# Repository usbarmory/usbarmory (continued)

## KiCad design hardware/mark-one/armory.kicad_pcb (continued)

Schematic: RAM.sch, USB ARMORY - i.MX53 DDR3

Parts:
C89, C90, C91, C93, C94, C96, C97, C98, C100, C101, C102, C104: 0.1uF; SM0201; Mfg PN C0603X5R0J104K030BC
C95, C99, C103: 0.01uF; SM0201; Mfg PN C0603X7R1A103K030BA
C105, C106: 10uF; SM0603; Mfg PN C1608X5R1A106K080AC
P3: TST; TP
R15, R24: 470; SM0201; Mfg PN CRCW0201470RFNED
R27, R29: 240; SM0201; Mfg PN CRCW0201240RFNED
R30: 100; SM0603; Mfg PN CRCW0603100RFKEA
U2: MX53
U4: MT41K256M16HA; micron-96-fbga-ha; Mfg PN MT41K256M16HA-107

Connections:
/RAM/DDR_VREF: C89.1, C90.2, C91.1, C93.1, P3.1, R15.1, R24.2, U2.L17 (DDR_VREF), U4.H1 (VREFDQ), U4.M8 (VREFCA)
/RAM/DDR_ZQ: R29.2, U4.L8 (ZQ)
/RAM/DRAM_A0: U2.M19 (DRAM_A0), U4.N3 (A0)
/RAM/DRAM_A1: U2.L21 (DRAM_A1), U4.P7 (A1)
/RAM/DRAM_A2: U2.M20 (DRAM_A2), U4.P3 (A2)
/RAM/DRAM_A3: U2.N20 (DRAM_A3), U4.N2 (A3)
/RAM/DRAM_A4: U2.K20 (DRAM_A4), U4.P8 (A4)
/RAM/DRAM_A5: U2.N21 (DRAM_A5), U4.P2 (A5)
/RAM/DRAM_A6: U2.M22 (DRAM_A6), U4.R8 (A6)
/RAM/DRAM_A7: U2.N22 (DRAM_A7), U4.R2 (A7)
/RAM/DRAM_A8: U2.N23 (DRAM_A8), U4.T8 (A8)
/RAM/DRAM_A9: U2.M21 (DRAM_A9), U4.R3 (A9)
/RAM/DRAM_A10: U2.K19 (DRAM_A10), U4.L7 (A10/AP)
/RAM/DRAM_A11: U2.L22 (DRAM_A11), U4.R7 (A11)
/RAM/DRAM_A12: U2.L20 (DRAM_A12), U4.N7 (A12/~BC)
/RAM/DRAM_A13: U2.L23 (DRAM_A13), U4.T3 (A13)
/RAM/DRAM_A14: U2.N18 (DRAM_A14), U4.T7 (A14)
/RAM/DRAM_CALIBRATION: R27.2, U2.M23 (DRAM_CALIBRATION)
/RAM/DRAM_CAS: U2.L18 (DRAM_CAS), U4.K3 (~CAS)
/RAM/DRAM_CS0: U2.K18 (DRAM_CS0), U4.L2 (~CS)
/RAM/DRAM_D0: U2.H20 (DRAM_D0), U4.E3 (DQ0)
/RAM/DRAM_D1: U2.G21 (DRAM_D1), U4.F7 (DQ1)
/RAM/DRAM_D2: U2.J21 (DRAM_D2), U4.F2 (DQ2)
/RAM/DRAM_D3: U2.G20 (DRAM_D3), U4.F8 (DQ3)
/RAM/DRAM_D4: U2.J23 (DRAM_D4), U4.H3 (DQ4)
/RAM/DRAM_D5: U2.G23 (DRAM_D5), U4.H8 (DQ5)
/RAM/DRAM_D6: U2.J22 (DRAM_D6), U4.G2 (DQ6)
/RAM/DRAM_D7: U2.G22 (DRAM_D7), U4.H7 (DQ7)
/RAM/DRAM_D8: U2.E21 (DRAM_D8), U4.D7 (DQ8)
/RAM/DRAM_D9: U2.D21 (DRAM_D9), U4.C3 (DQ9)
/RAM/DRAM_D10: U2.E22 (DRAM_D10), U4.C8 (DQ10)
/RAM/DRAM_D11: U2.D20 (DRAM_D11), U4.C2 (DQ11)
/RAM/DRAM_D12: U2.E23 (DRAM_D12), U4.A7 (DQ12)
/RAM/DRAM_D13: U2.C23 (DRAM_D13), U4.A2 (DQ13)
/RAM/DRAM_D14: U2.F23 (DRAM_D14), U4.B8 (DQ14)
/RAM/DRAM_D15: U2.C22 (DRAM_D15), U4.A3 (DQ15)
/RAM/DRAM_DQM0: U2.H21 (DRAM_DQM0), U4.E7 (LDM)
/RAM/DRAM_DQM1: U2.E20 (DRAM_DQM1), U4.D3 (UDM)
/RAM/DRAM_RAS: U2.J19 (DRAM_RAS), U4.J3 (~RAS)
/RAM/DRAM_RESET: U2.P18 (DRAM_RESET), U4.T2 (~RESET)
/RAM/DRAM_SDBA0: U2.R19 (DRAM_SDBA0), U4.M2 (BA0)
/RAM/DRAM_SDBA1: U2.P20 (DRAM_SDBA1), U4.N8 (BA1)
/RAM/DRAM_SDBA2: U2.N19 (DRAM_SDBA2), U4.M3 (BA2)
/RAM/DRAM_SDCKE0: U2.H19 (DRAM_SDCKE0), U4.K9 (CKE)
/RAM/DRAM_SDCLK_0: R30.1, U2.K23 (DRAM_SDCLK_0), U4.J7 (CK)
/RAM/DRAM_SDCLK_0_B: R30.2, U2.K22 (~DRAM_SDCLK_0_B), U4.K7 (~CK)
/RAM/DRAM_SDODT0: U2.J18 (DRAM_SDODT0), U4.K1 (ODT)
/RAM/DRAM_SDQS0: U2.H23 (DRAM_SDQS0), U4.F3 (LDQS)
/RAM/DRAM_SDQS0_B: U2.H22 (~DRAM_SDQS0_B), U4.G3 (~LDQS)
/RAM/DRAM_SDQS1: U2.D23 (DRAM_SDQS1), U4.C7 (UDQS)
/RAM/DRAM_SDQS1_B: U2.D22 (~DRAM_SDQS1_B), U4.B7 (~UDQS)
/RAM/DRAM_WE: U2.L19 (DRAM_SDWE), U4.L3 (~WE)
GND: C89.2, C91.2, C93.2, C94.2, C95.2, C96.2, C97.2, C98.2, C99.2, C100.2, C101.2, C102.2, C103.2, C104.2, C105.2, C106.2, R24.1, R27.1, R29.1, U4.A9 (VSS1), U4.B1 (VSSQ1), U4.B3 (VSS2), U4.B9 (VSSQ2), U4.D1 (VSSQ3), U4.D8 (VSSQ4), U4.E1 (VSS3), U4.E2 (VSSQ5), U4.E8 (VSSQ6), U4.F9 (VSSQ7), U4.G1 (VSSQ8), U4.G8 (VSS4), U4.G9 (VSSQ9), U4.J2 (VSS5), U4.J8 (VSS6), U4.M9 (VSS8), U4.P1 (VSS9), U4.P9 (VSS10), U4.T1 (VSS11), U4.T9 (VSS12); also elsewhere on the board
PMIC_DDR_1V5: C90.1, C94.1, C95.1, C96.1, C97.1, C98.1, C99.1, C100.1, C101.1, C102.1, C103.1, C104.1, C105.1, C106.1, R15.2, U4.A1 (VDDQ1), U4.A8 (VDDQ2), U4.B2 (VDD1), U4.C1 (VDDQ3), U4.C9 (VDDQ4), U4.D2 (VDDQ5), U4.D9 (VDD2), U4.E9 (VDDQ6), U4.F1 (VDDQ7), U4.G7 (VDD3), U4.H2 (VDDQ8), U4.H9 (VDDQ9), U4.K2 (VDD4), U4.K8 (VDD5), U4.N1 (VDD6), U4.N9 (VDD7), U4.R1 (VDD8), U4.R9 (VDD9); also elsewhere on the board

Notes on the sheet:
Place near the VDD balls.
Place near the VDDQ balls.

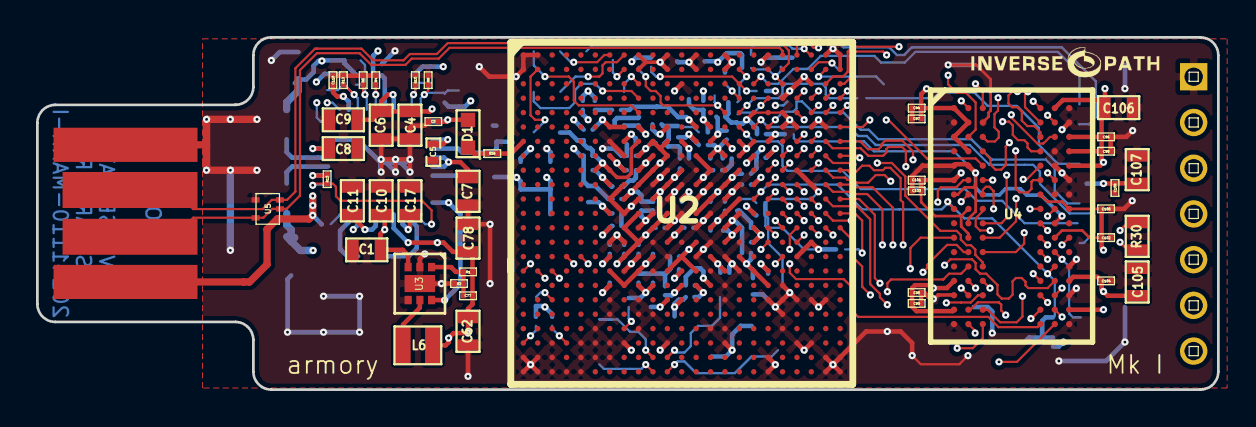
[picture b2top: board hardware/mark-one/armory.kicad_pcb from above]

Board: 8 copper layers, 65.6 x 19.6 mm, 186 parts (0 on the bottom side), 126 nets.

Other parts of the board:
Ref**: Val**; LOGO_SMALL

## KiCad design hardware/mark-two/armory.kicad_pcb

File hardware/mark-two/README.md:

Introduction
============

The USB armory is an open source hardware design, implementing a flash drive
sized computer.

This repository is aimed towards developers, if you wish to purchase a USB
armory board please see the [ordering information](https://github.com/usbarmory/usbarmory/wiki/Ordering-information).

Authors
=======

Andrea Barisani  
andrea@inversepath.com  

Andrej Rosano  
andrej@inversepath.com  

Daniele Bianco  
daniele@inversepath.com  

Documentation
=============

The main documentation can be found on the
[project wiki](https://github.com/usbarmory/usbarmory/wiki).

Revision information
====================

This directory contains the hardware design for the USB armory Mk II rev. γ.

Current schematics and layout files have been designed in KiCad 5.1.10.

PCB Information
===============

6 layers, 0.8mm thickness  
Outer layers 0.5 oz base copper foil  
Inner layers   1 oz base copper foil  
width (X) 65.6 mm, height (Y) 19.5 mm  
Electroless Nickel Immersion Gold (ENIG) surface finish  
Black resist, white component legend

Layers
------

Order and type of copper layers:  
  TOP:         signal, front components  
  SIGNAL 1:    signal  
  GND POWER 1: ground and power plane  
  GND POWER 2: ground and power plane  
  SIGNAL 2:    signal  
  BOTTOM:      signal, back components  

| Layer | Description               |  Thickness (in um)  |
|:-----:|---------------------------|:-------------------:|
|       | LPI mask                  |   15                |
|       | ENIG plating              |   18                |
|   1   | copper                    |   30                |
|       | prepreg, 2 x PP 106       |  121                |
|   2   | copper                    |   17                |
|       | core, FR4 17/17           |  125                |
|   3   | copper                    |   17                |
|       | prepreg, 2 x PP 106       |  116                |
|   4   | copper                    |   17                |
|       | core, FR4 17/17           |  125                |
|   5   | copper                    |   17                |
|       | prepreg, 2 x PP 106       |  121                |
|   6   | copper                    |   30                |
|       | ENIG plating              |   18                |
|       | LPI mask                  |   15                |

Material: Isola PCL370-HR
Total thickness: 0.8 mm

DRC information
---------------

Minimum track width:            0.100 mm  
Minimum via diameter:           0.406 mm  
Outer layer track width:        0.100 mm  
Outer layer isolation distance: 0.100 mm  
Outer layer annular ring:       0.075 mm  
Inner layer track width:        0.100 mm  
Inner layer isolation distance: 0.100 mm  
Inner layer annular ring:       0.075 mm  
Smallest final hole (plated):   0.150 mm

Regulatory compliance & handling
================================

The USB armory board is an open system design, which does not include a
shielded enclosure. This may cause interference to other electrical or
electronic devices in close proximity. In a domestic environment, this product
may cause radio interference in which case the user may be required to take
adequate measures. In addition, this board should not be used near any medical
equipment or RF devices.

The board is sensitive to Electrostatic discharge (ESD). Hold the board only by
its edges. After removing the board from its box, place it on a grounded,
static-free surface.

The board can become hot, like any fan-less design, during continuous high CPU
loads, mind its temperature while handling it.

* [Compliance information](https://github.com/usbarmory/usbarmory/wiki/Compliance-information)

License
=======

USB armory | https://github.com/usbarmory/usbarmory  
Copyright (c) The USB armory authors

This source describes Open Hardware and is licensed under the CERN-OHL-S v2.

You may redistribute and modify this source and make products using it under
the terms of the CERN-OHL-S v2 (https://ohwr.org/cern_ohl_s_v2.txt).

This source is distributed WITHOUT ANY EXPRESS OR IMPLIED WARRANTY, INCLUDING
OF MERCHANTABILITY, SATISFACTORY QUALITY AND FITNESS FOR A PARTICULAR PURPOSE.
Please see the CERN-OHL-S v2 for applicable conditions.

As per CERN-OHL-S v2 section 4, should You produce hardware based on this
source, You must where practicable maintain the Source Location visible on the
external case of the USB armory or other products you make using this source.

The following exceptions apply:

- `../lib.snapeda`: all files in this directory are imported or modified
  from SnapEDA symbols and footprints, therefore the license at
  https://www.snapeda.com/about/FAQ/#license applies.

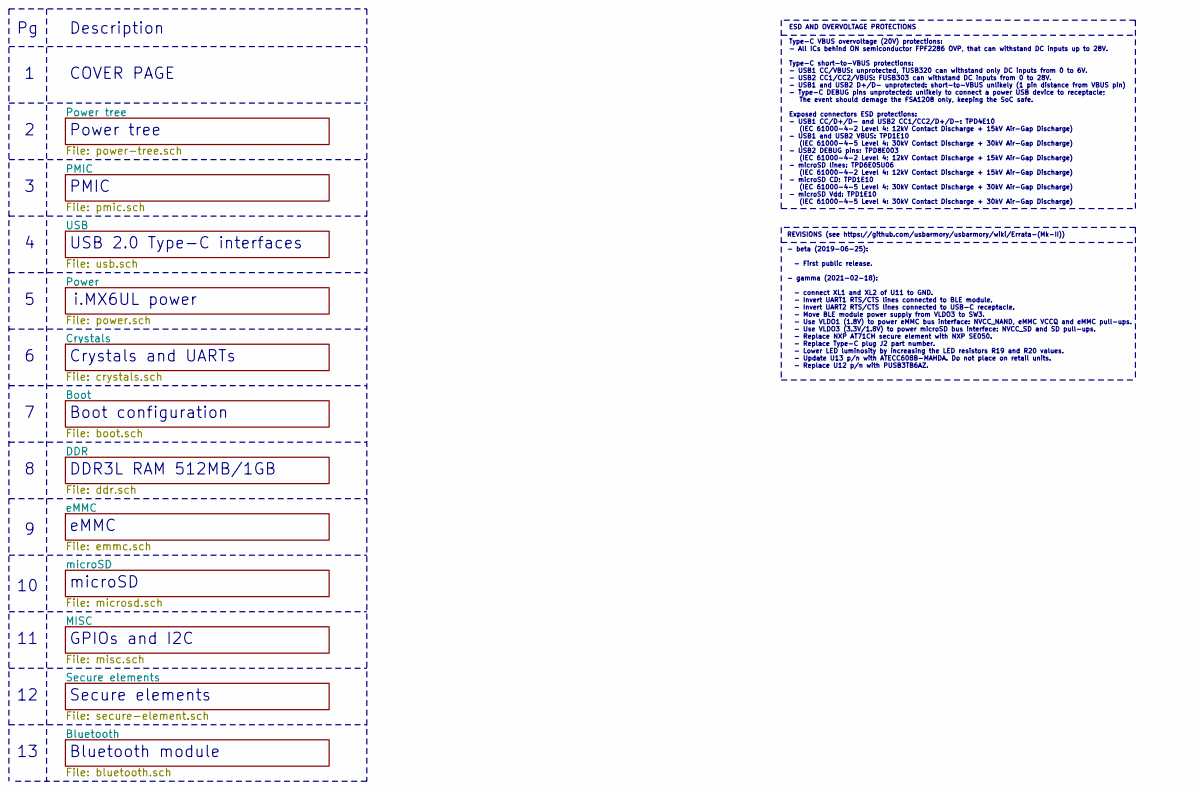
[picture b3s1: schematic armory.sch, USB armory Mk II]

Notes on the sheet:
microSD
DDR3L RAM 512MB/1GB
eMMC
Secure elements
Bluetooth module
Boot configuration
GPIOs and I2C
i.MX6UL power
USB 2.0 Type-C interfaces
Crystals and UARTs
ESD AND OVERVOLTAGE PROTECTIONS Type-C VBUS overvoltage (20V) protections: - All ICs behind ON semiconductor FPF2286 OVP, that can withstand DC inputs up to 28V. Type-C short-to-VBUS protections: - USB1 CC/VBUS: unprotected, TUSB320 can withstand only DC inputs from 0 to 6V. - USB2 CC1/CC2/VBUS: FU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
PMIC
Description
Power tree
COVER PAGE
REVISIONS (see https://github.com/usbarmory/usbarmory/wiki/Errata-(Mk-II)) - beta (2019-06-25): - First public release. - gamma (2021-02-18): - connect XL1 and XL2 of U11 to GND. - Invert UART1 RTS/CTS lines connected to BLE module. - Invert UART2 RTS/CTS lines connected to USB-C receptacle. - Move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

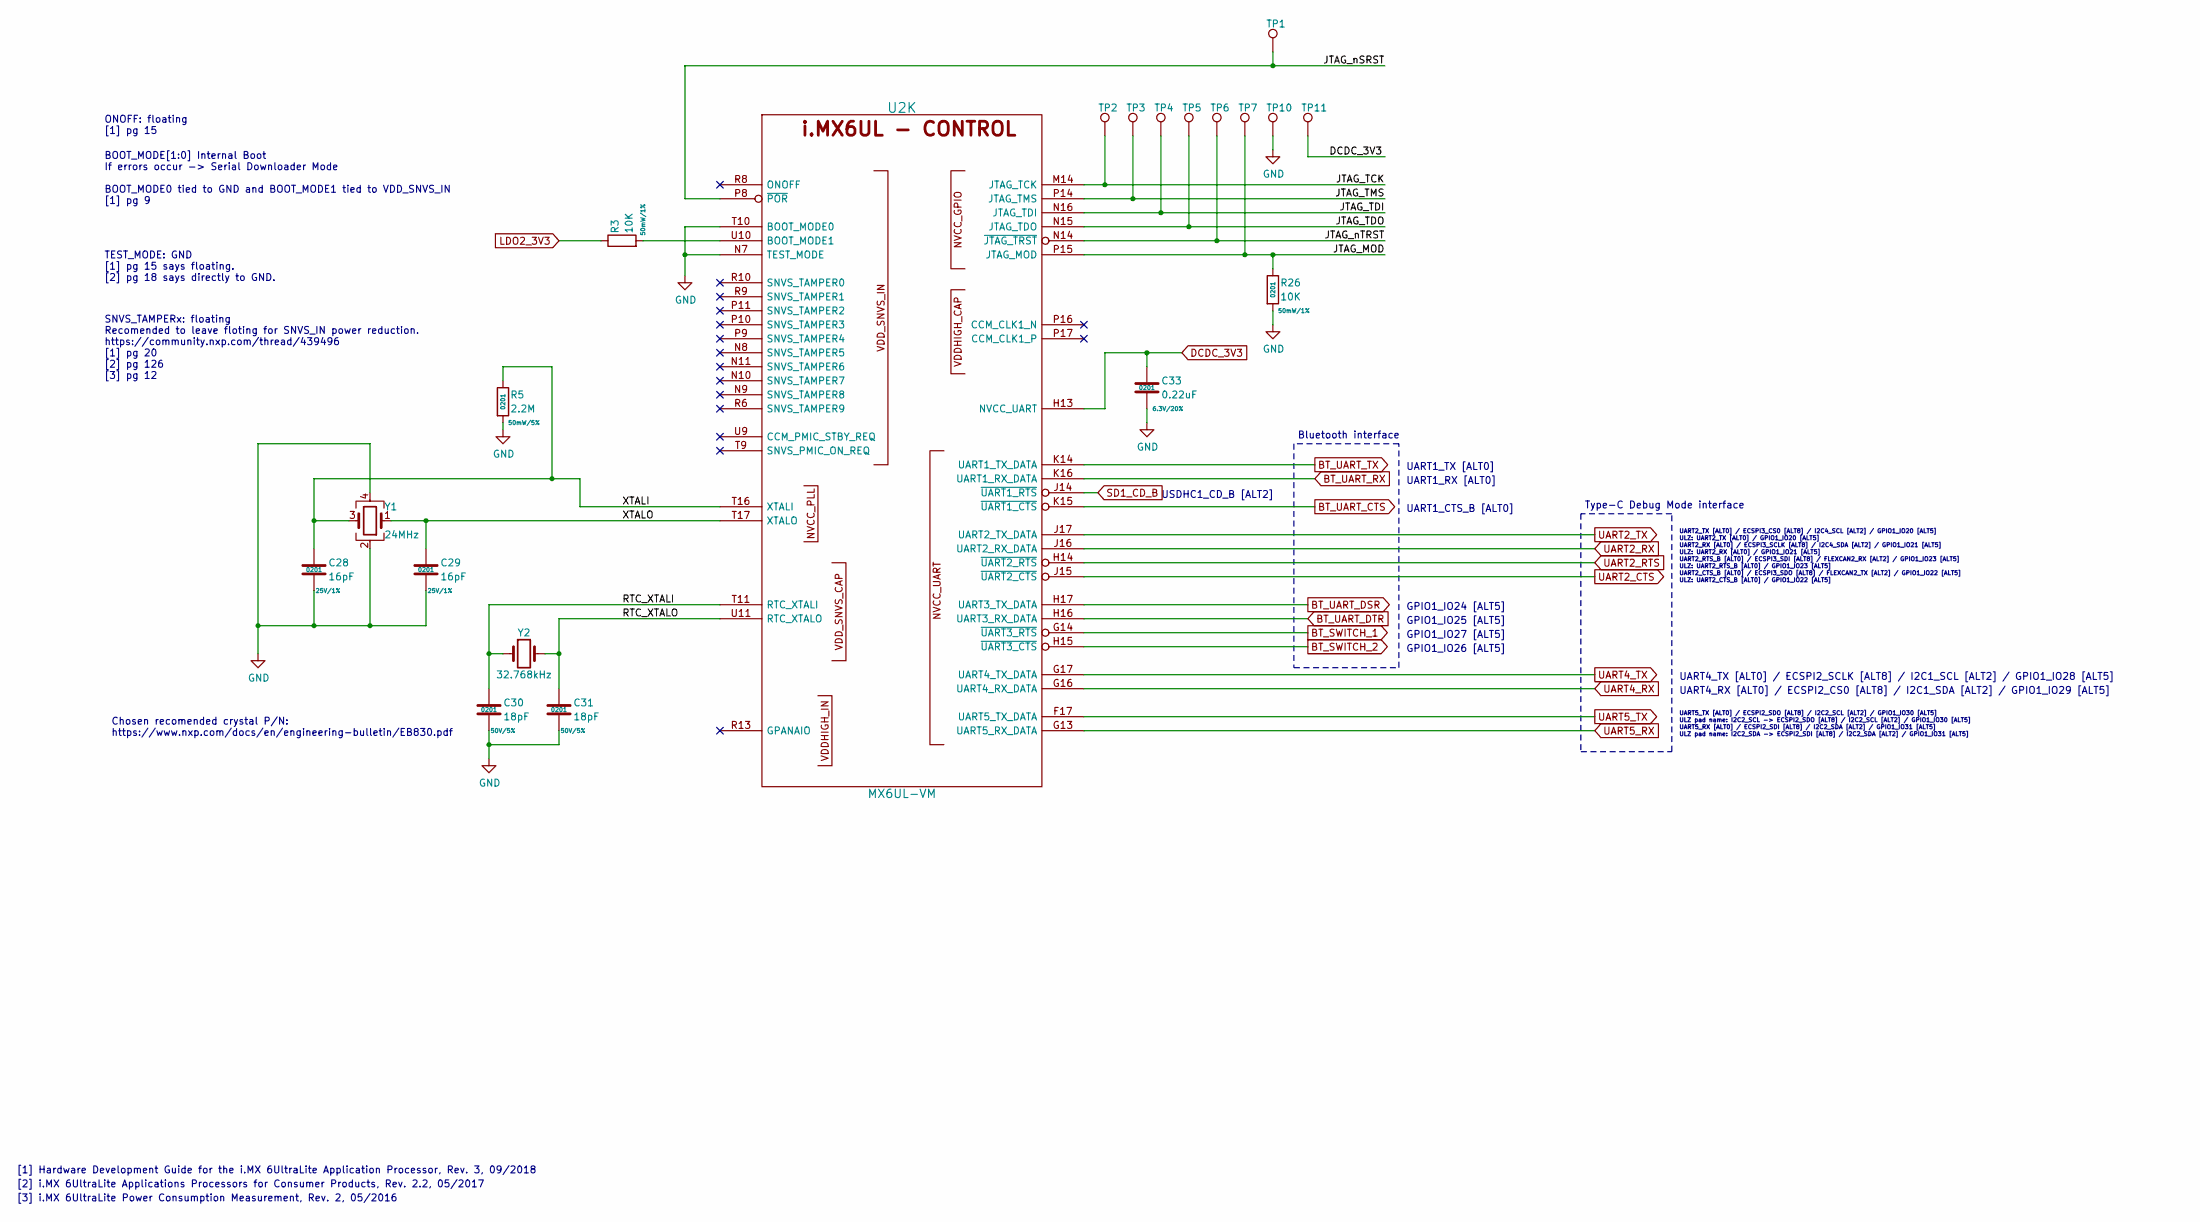
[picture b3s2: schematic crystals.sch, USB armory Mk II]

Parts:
C28, C29: 16pF; SM0201; Rating 25V/1%; Mfg PN CBR02C160F3GAC
C30, C31: 18pF; SM0201; Rating 50V/5%; Mfg PN GRM0335C1H180JA01D
C33: 0.22uF; SM0201; Rating 6.3V/20%; Mfg PN GRM033R60J224ME15D
R3, R26: 10K; SM0201; Rating 50mW/1%; Mfg PN CRCW020110K0JNED
R5: 2.2M; SM0201; Rating 50mW/5%; Mfg PN RC0201JR-072M2L
TP1, TP2, TP3, TP4, TP5, TP6, TP7, TP10, TP11: TestPoint; TP
U2: MX6UL-VM; SOT1534-2; Mfg PN MCIMX6Z0DVM09AB
Y1: 24MHz; TSX-3225; Mfg PN TSX-3225 24.0000MF15X-AC3
Y2: 32.768kHz; CM7V-T1A; Mfg PN CM7V-T1A-32.768kHz-12.5pF-20PPM-TA-QC

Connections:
/Crystals/JTAG_MOD: R26.1, TP7.1, U2.P15 (JTAG_MOD)
/Crystals/JTAG_TCK: TP2.1, U2.M14 (JTAG_TCK)
/Crystals/JTAG_TDI: TP4.1, U2.N16 (JTAG_TDI)
/Crystals/JTAG_TDO: TP5.1, U2.N15 (JTAG_TDO)
/Crystals/JTAG_TMS: TP3.1, U2.P14 (JTAG_TMS)
/Crystals/JTAG_nSRST: TP1.1, U2.P8 (~POR)
/Crystals/JTAG_nTRST: TP6.1, U2.N14 (~JTAG_TRST)
/Crystals/RTC_XTALI: C30.1, U2.T11 (RTC_XTALI), Y2.1
/Crystals/RTC_XTALO: C31.1, U2.U11 (RTC_XTALO), Y2.2
/Crystals/XTALI: C28.1, R5.1, U2.T16 (XTALI), Y1.3
/Crystals/XTALO: C29.1, U2.T17 (XTALO), Y1.1
BT_SWITCH_1: U2.G14 (~UART3_RTS); also elsewhere on the board
BT_SWITCH_2: U2.H15 (~UART3_CTS); also elsewhere on the board
BT_UART_CTS: U2.K15 (~UART1_CTS); also elsewhere on the board
BT_UART_DSR: U2.H17 (UART3_TX_DATA); also elsewhere on the board
BT_UART_DTR: U2.H16 (UART3_RX_DATA); also elsewhere on the board
BT_UART_RX: U2.K16 (UART1_RX_DATA); also elsewhere on the board
BT_UART_TX: U2.K14 (UART1_TX_DATA); also elsewhere on the board
DCDC_3V3: C33.1, TP11.1, U2.H13 (NVCC_UART); also elsewhere on the board
GND: C28.2, C29.2, C30.2, C31.2, C33.2, R5.2, R26.2, TP10.1, U2.N7 (TEST_MODE), U2.T10 (BOOT_MODE0), Y1.2, Y1.4; also elsewhere on the board
LDO2_3V3: R3.1; also elsewhere on the board
unnamed: R3.2, U2.U10 (BOOT_MODE1)
SD1_CD_B: U2.J14 (~UART1_RTS); also elsewhere on the board
UART2_CTS: U2.J15 (~UART2_CTS); also elsewhere on the board
UART2_RTS: U2.H14 (~UART2_RTS); also elsewhere on the board
UART2_RX: U2.J16 (UART2_RX_DATA); also elsewhere on the board
UART2_TX: U2.J17 (UART2_TX_DATA); also elsewhere on the board
UART4_RX: U2.G16 (UART4_RX_DATA); also elsewhere on the board
UART4_TX: U2.G17 (UART4_TX_DATA); also elsewhere on the board
UART5_RX: U2.G13 (UART5_RX_DATA); also elsewhere on the board
UART5_TX: U2.F17 (UART5_TX_DATA); also elsewhere on the board

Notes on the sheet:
BOOT_MODE[1:0] Internal Boot If errors occur -> Serial Downloader Mode BOOT_MODE0 tied to GND and BOOT_MODE1 tied to VDD_SNVS_IN [1] pg 9
TEST_MODE: GND [1] pg 15 says floating. [2] pg 18 says directly to GND.
[1] Hardware Development Guide for the i.MX 6UltraLite Application Processor, Rev. 3, 09/2018
SNVS_TAMPERx: floating Recomended to leave floting for SNVS_IN power reduction. https://community.nxp.com/thread/439496 [1] pg 20 [2] pg 126 [3] pg 12
[2] i.MX 6UltraLite Applications Processors for Consumer Products, Rev. 2.2, 05/2017
Bluetooth interface
GPIO1_IO24 [ALT5]
GPIO1_IO25 [ALT5]
GPIO1_IO26 [ALT5]
GPIO1_IO27 [ALT5]
UART1_TX [ALT0]
UART1_CTS_B [ALT0]
ONOFF: floating [1] pg 15
[3] i.MX 6UltraLite Power Consumption Measurement, Rev. 2, 05/2016
UART1_RX [ALT0]
USDHC1_CD_B [ALT2]
ULZ pad name: I2C2_SDA -> ECSPI2_SDI [ALT8] / I2C2_SDA [ALT2] / GPIO1_IO31 [ALT5]
ULZ pad name: I2C2_SCL -> ECSPI2_SDO [ALT8] / I2C2_SCL [ALT2] / GPIO1_IO30 [ALT5]
UART4_TX [ALT0] / ECSPI2_SCLK [ALT8] / I2C1_SCL [ALT2] / GPIO1_IO28 [ALT5]
ULZ: UART2_CTS_B [ALT0] / GPIO1_IO22 [ALT5]
ULZ: UART2_RTS_B [ALT0] / GPIO1_IO23 [ALT5]
ULZ: UART2_RX [ALT0] / GPIO1_IO21 [ALT5]
Type-C Debug Mode interface
UART5_RX [ALT0] / ECSPI2_SDI [ALT8] / I2C2_SDA [ALT2] / GPIO1_IO31 [ALT5]
UART5_TX [ALT0] / ECSPI2_SDO [ALT8] / I2C2_SCL [ALT2] / GPIO1_IO30 [ALT5]
UART4_RX [ALT0] / ECSPI2_CS0 [ALT8] / I2C1_SDA [ALT2] / GPIO1_IO29 [ALT5]
UART2_RTS_B [ALT0] / ECSPI3_SDI [ALT8] / FLEXCAN2_RX [ALT2] / GPIO1_IO23 [ALT5]
UART2_CTS_B [ALT0] / ECSPI3_SDO [ALT8] / FLEXCAN2_TX [ALT2] / GPIO1_IO22 [ALT5]
UART2_RX [ALT0] / ECSPI3_SCLK [ALT8] / I2C4_SDA [ALT2] / GPIO1_IO21 [ALT5]
UART2_TX [ALT0] / ECSPI3_CS0 [ALT8] / I2C4_SCL [ALT2] / GPIO1_IO20 [ALT5]
ULZ: UART2_TX [ALT0] / GPIO1_IO20 [ALT5]
Chosen recomended crystal P/N: https://www.nxp.com/docs/en/engineering-bulletin/EB830.pdf

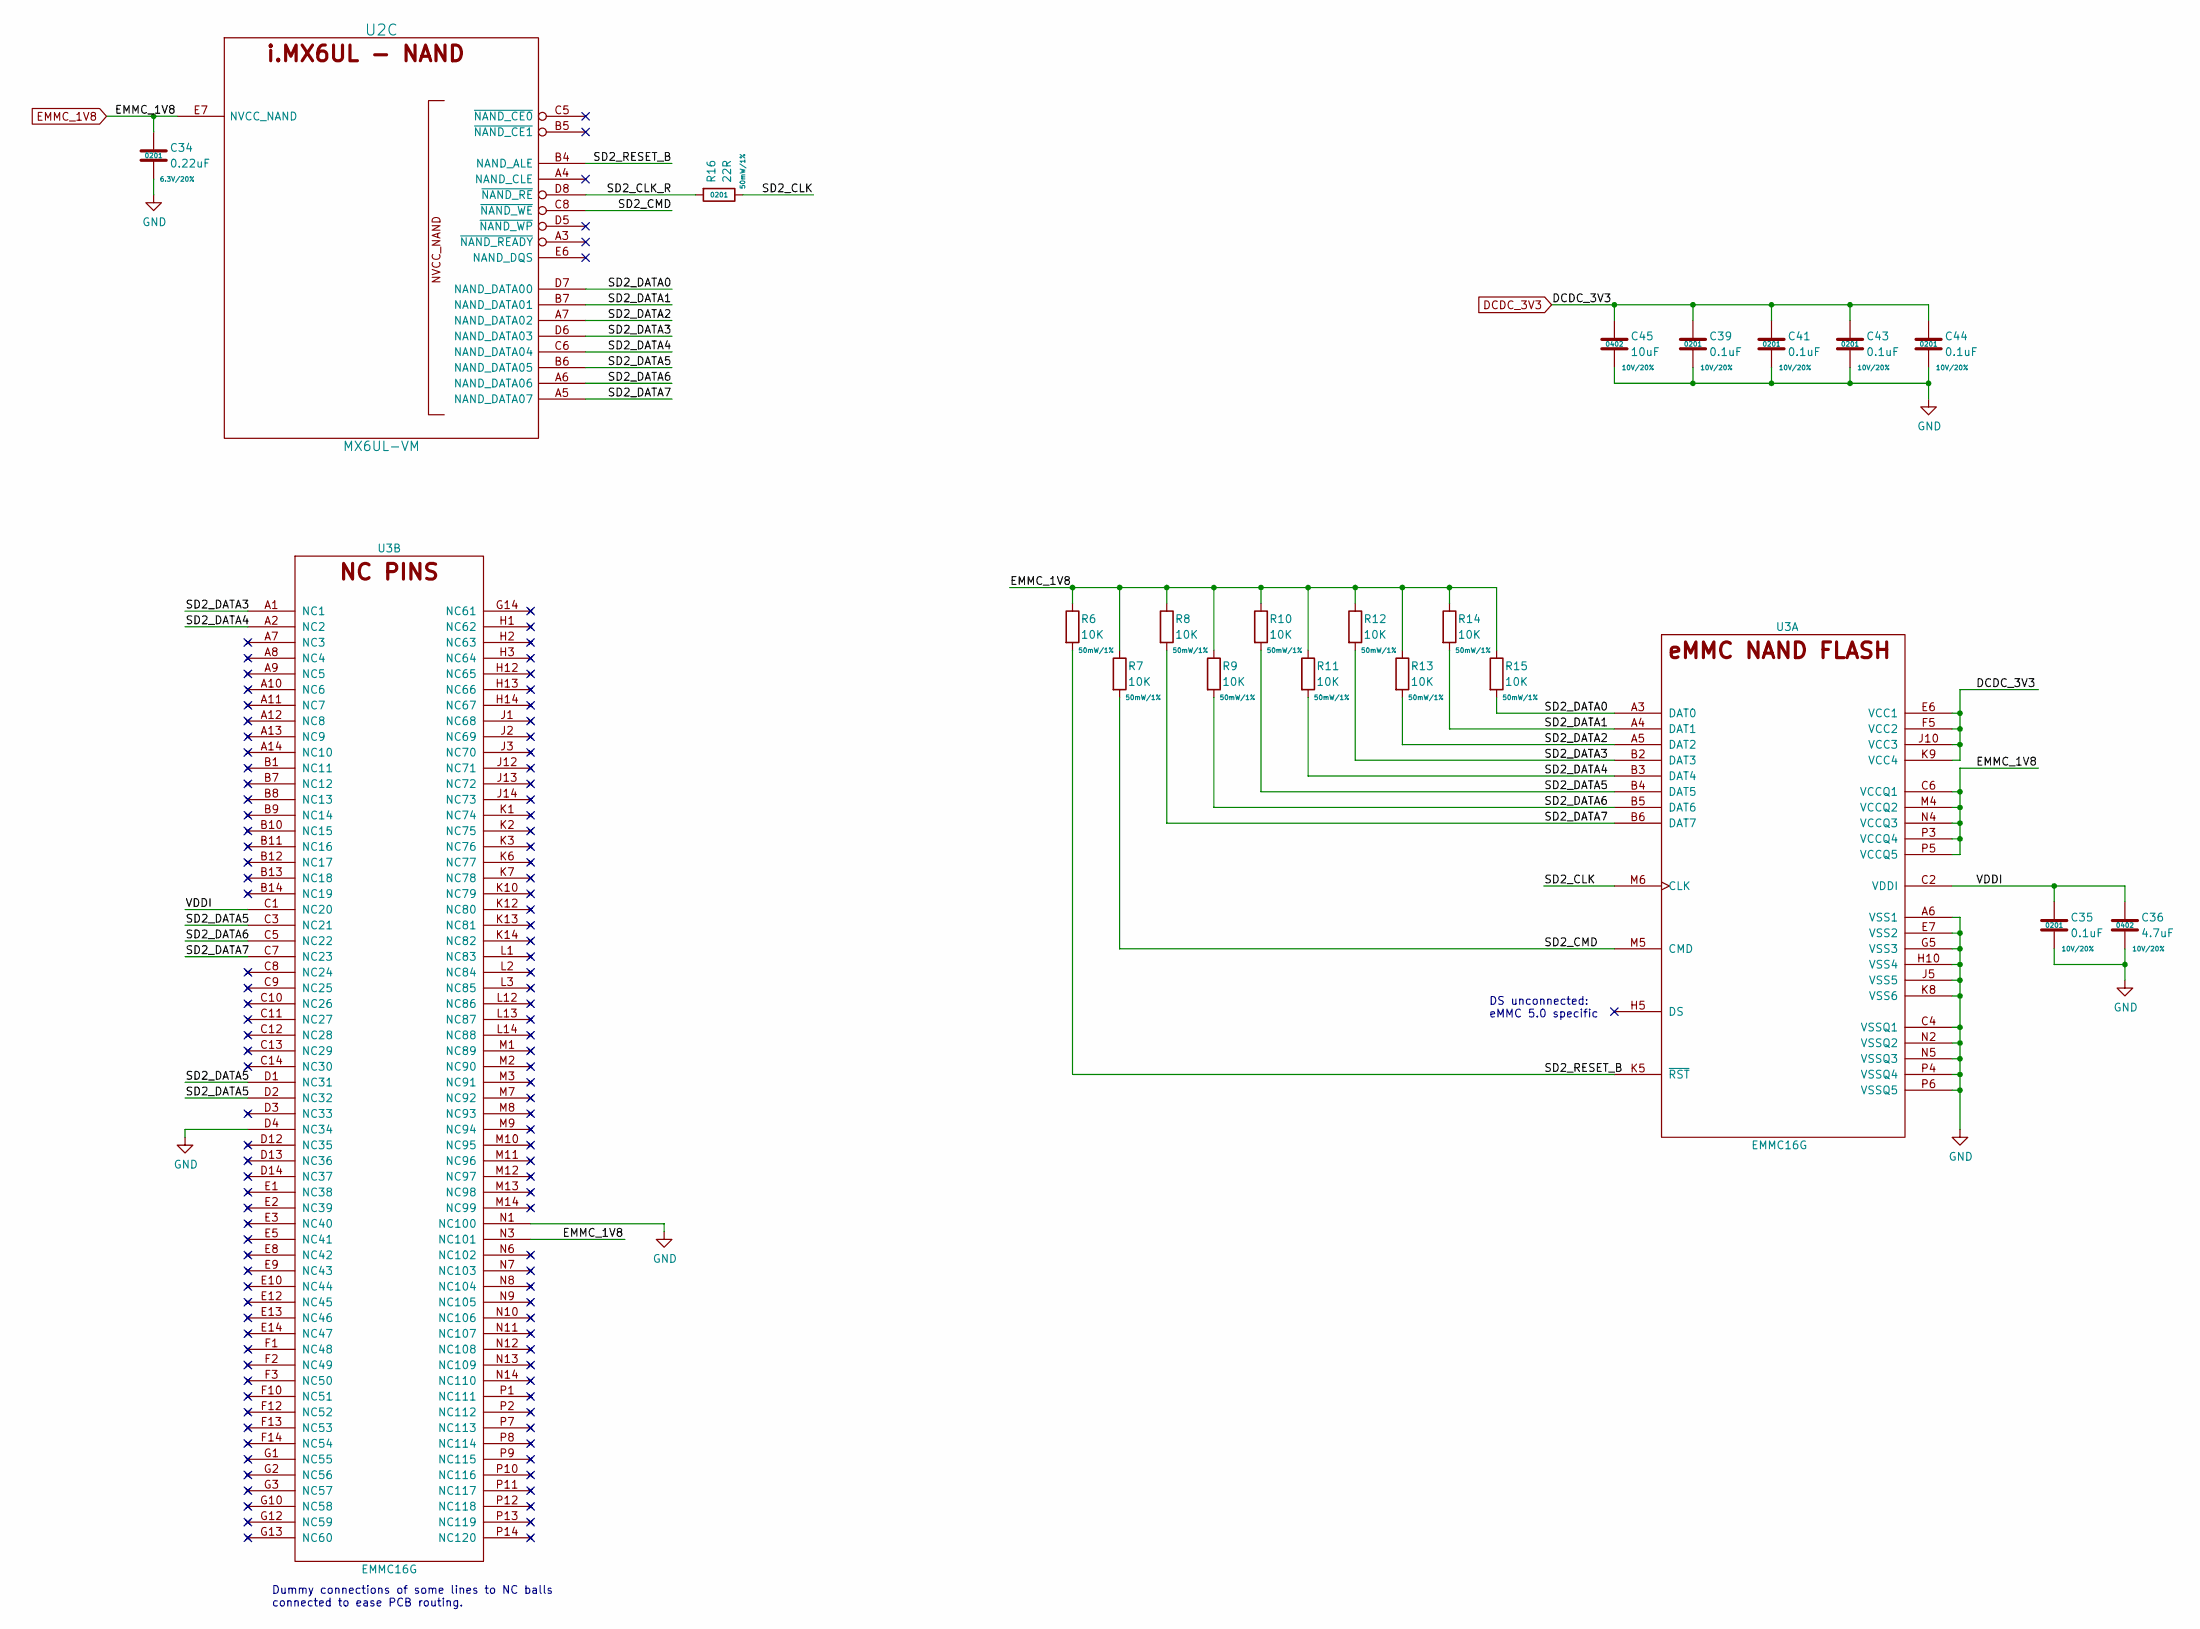
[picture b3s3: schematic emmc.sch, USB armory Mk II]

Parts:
C34: 0.22uF; SM0201; Rating 6.3V/20%; Mfg PN GRM033R60J224ME15D
C35, C39, C41, C43, C44: 0.1uF; SM0201; Rating 10V/20%; Mfg PN GRM033R61A104ME15D
C36: 4.7uF; SM0402; Rating 10V/20%; Mfg PN ZRB15XR61A475ME01D
C45: 10uF; SM0402; Rating 10V/20%; Mfg PN CL05A106MP8NUB8
R6, R7, R8, R9, R10, R11, R12, R13, R14, R15: 10K; SM0201; Rating 50mW/1%; Mfg PN CRCW020110K0JNED
R16: 22R; SM0201; Rating 50mW/1%; Mfg PN CRCW020122R0JNED
U2: MX6UL-VM; SOT1534-2; Mfg PN MCIMX6Z0DVM09AB
U3: EMMC16G; FBGA-153; Mfg PN EMMC16G-TB29-PZ90

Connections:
/eMMC/SD2_CLK: R16.1, U3.M6 (CLK)
/eMMC/SD2_CLK_R: R16.2, U2.D8 (~NAND_RE)
/eMMC/SD2_CMD: R7.2, U2.C8 (~NAND_WE), U3.M5 (CMD)
/eMMC/SD2_DATA0: R15.2, U2.D7 (NAND_DATA00), U3.A3 (DAT0)
/eMMC/SD2_DATA1: R14.2, U2.B7 (NAND_DATA01), U3.A4 (DAT1)
/eMMC/SD2_DATA2: R13.2, U2.A7 (NAND_DATA02), U3.A5 (DAT2)
/eMMC/SD2_DATA3: R12.2, U2.D6 (NAND_DATA03), U3.A1 (NC1), U3.B2 (DAT3)
/eMMC/SD2_DATA4: R11.2, U2.C6 (NAND_DATA04), U3.A2 (NC2), U3.B3 (DAT4)
/eMMC/SD2_DATA5: R10.2, U2.B6 (NAND_DATA05), U3.B4 (DAT5), U3.C3 (NC21), U3.D1 (NC31), U3.D2 (NC32)
/eMMC/SD2_DATA6: R9.2, U2.A6 (NAND_DATA06), U3.B5 (DAT6), U3.C5 (NC22)
/eMMC/SD2_DATA7: R8.2, U2.A5 (NAND_DATA07), U3.B6 (DAT7), U3.C7 (NC23)
/eMMC/SD2_RESET_B: R6.2, U2.B4 (NAND_ALE), U3.K5 (~RST)
/eMMC/VDDI: C35.1, C36.1, U3.C1 (NC20), U3.C2 (VDDI)
DCDC_3V3: C39.1, C41.1, C43.1, C44.1, C45.1, U3.E6 (VCC1), U3.F5 (VCC2), U3.J10 (VCC3), U3.K9 (VCC4); also elsewhere on the board
EMMC_1V8: C34.1, R6.1, R7.1, R8.1, R9.1, R10.1, R11.1, R12.1, R13.1, R14.1, R15.1, U2.E7 (NVCC_NAND), U3.C6 (VCCQ1), U3.M4 (VCCQ2), U3.N3 (NC101), U3.N4 (VCCQ3), U3.P3 (VCCQ4), U3.P5 (VCCQ5); also elsewhere on the board
GND: C34.2, C35.2, C36.2, C39.2, C41.2, C43.2, C44.2, C45.2, U3.A6 (VSS1), U3.C4 (VSSQ1), U3.D4 (NC34), U3.E7 (VSS2), U3.G5 (VSS3), U3.H10 (VSS4), U3.J5 (VSS5), U3.K8 (VSS6), U3.N1 (NC100), U3.N2 (VSSQ2), U3.N5 (VSSQ3), U3.P4 (VSSQ4), U3.P6 (VSSQ5); also elsewhere on the board

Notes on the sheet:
Dummy connections of some lines to NC balls connected to ease PCB routing.
DS unconnected: eMMC 5.0 specific

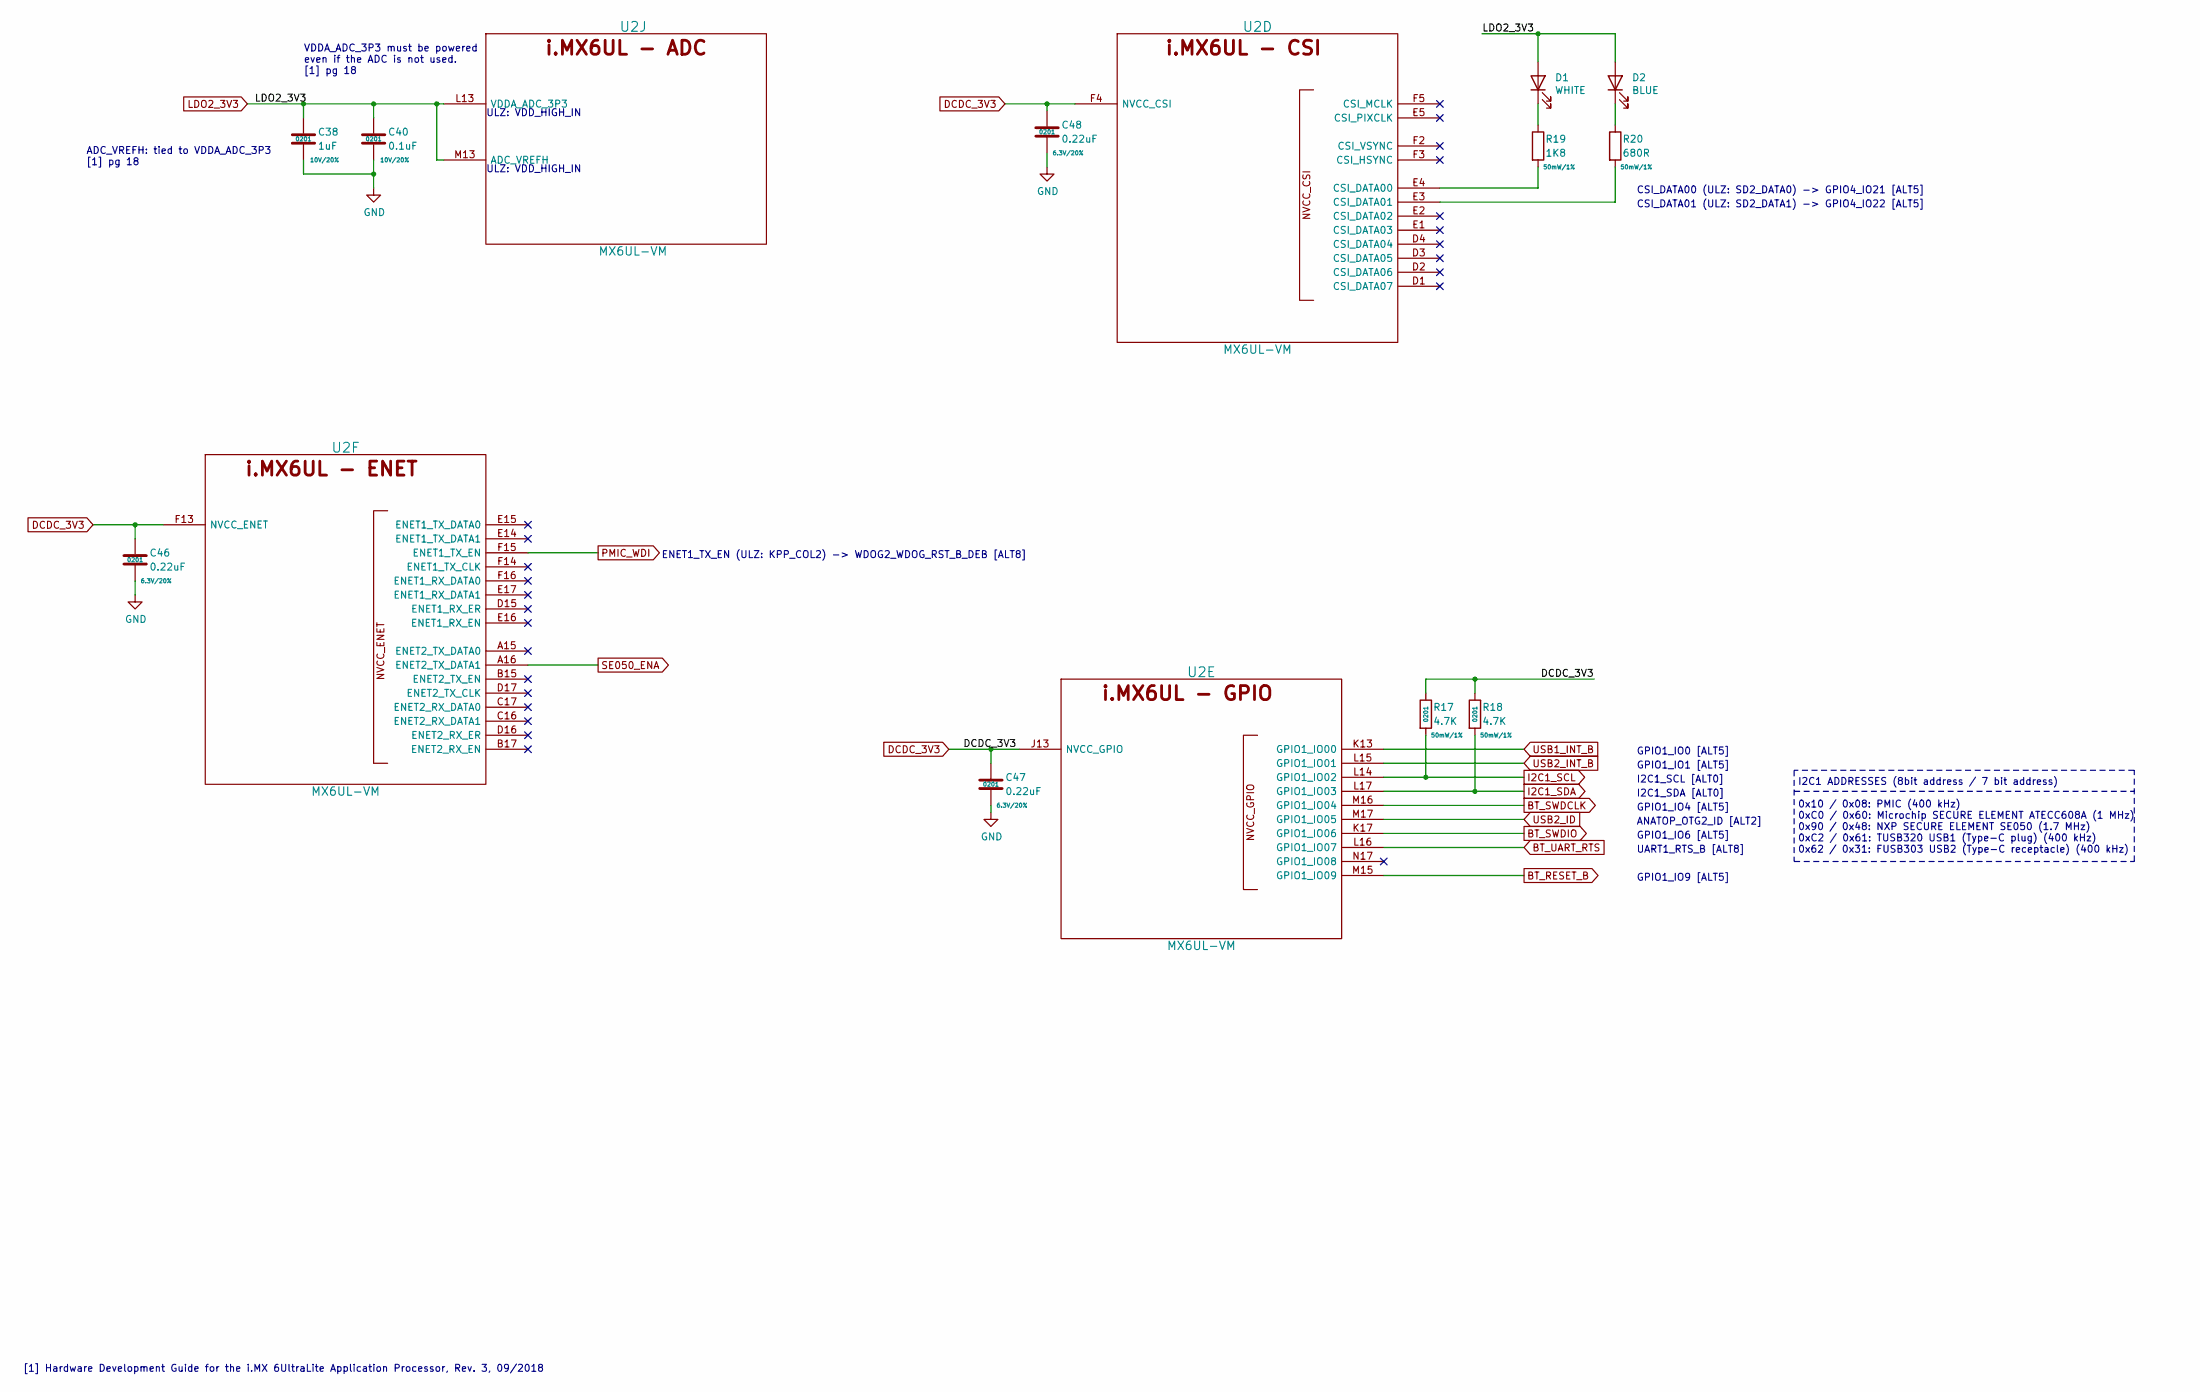
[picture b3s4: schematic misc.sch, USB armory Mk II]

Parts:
C38: 1uF; SM0201; Rating 10V/20%; Mfg PN GRM033R61A105ME15D
C40: 0.1uF; SM0201; Rating 10V/20%; Mfg PN GRM033R61A104ME15D
C46, C47, C48: 0.22uF; SM0201; Rating 6.3V/20%; Mfg PN GRM033R60J224ME15D
D1: WHITE; SM0603_LED; Rating 5mA/2.85V; Mfg PN LW Q38E-Q1OO-3K6L-1
D2: BLUE; SM0603_LED; Rating 5mA/2.85V; Mfg PN LB Q39G-L2OO-35-1
R17, R18: 4.7K; SM0201; Rating 50mW/1%; Mfg PN CRCW02014K70JNED
R19: 1K8; SM0201; Rating 50mW/1%; Mfg PN ERJ-1GNF1801C
R20: 680R; SM0201; Rating 50mW/1%; Mfg PN ERJ-1GNF6800C
U2: MX6UL-VM; SOT1534-2; Mfg PN MCIMX6Z0DVM09AB

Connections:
BT_RESET_B: U2.M15 (GPIO1_IO09); also elsewhere on the board
BT_SWDCLK: U2.M16 (GPIO1_IO04); also elsewhere on the board
BT_SWDIO: U2.K17 (GPIO1_IO06); also elsewhere on the board
BT_UART_RTS: U2.L16 (GPIO1_IO07); also elsewhere on the board
DCDC_3V3: C46.1, C47.1, C48.1, R17.1, R18.1, U2.F4 (NVCC_CSI), U2.F13 (NVCC_ENET), U2.J13 (NVCC_GPIO); also elsewhere on the board
GND: C38.2, C40.2, C46.2, C47.2, C48.2; also elsewhere on the board
I2C1_SCL: R17.2, U2.L14 (GPIO1_IO02); also elsewhere on the board
I2C1_SDA: R18.2, U2.L17 (GPIO1_IO03); also elsewhere on the board
LDO2_3V3: C38.1, C40.1, D1.2 (A), D2.2 (A), U2.L13 (VDDA_ADC_3P3), U2.M13 (ADC_VREFH); also elsewhere on the board
unnamed: D1.1 (K), R19.1
unnamed: D2.1 (K), R20.1
unnamed: R19.2, U2.E4 (CSI_DATA00)
unnamed: R20.2, U2.E3 (CSI_DATA01)
PMIC_WDI: U2.F15 (ENET1_TX_EN); also elsewhere on the board
SE050_ENA: U2.A16 (ENET2_TX_DATA1); also elsewhere on the board
USB1_INT_B: U2.K13 (GPIO1_IO00); also elsewhere on the board
USB2_ID: U2.M17 (GPIO1_IO05); also elsewhere on the board
USB2_INT_B: U2.L15 (GPIO1_IO01); also elsewhere on the board

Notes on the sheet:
[1] Hardware Development Guide for the i.MX 6UltraLite Application Processor, Rev. 3, 09/2018
ADC_VREFH: tied to VDDA_ADC_3P3 [1] pg 18
VDDA_ADC_3P3 must be powered even if the ADC is not used. [1] pg 18
I2C1_SCL [ALT0]
I2C1_SDA [ALT0]
GPIO1_IO9 [ALT5]
GPIO1_IO6 [ALT5]
GPIO1_IO4 [ALT5]
I2C1 ADDRESSES (8bit address / 7 bit address) 0x10 / 0x08: PMIC (400 kHz) 0xC0 / 0x60: Microchip SECURE ELEMENT ATECC608A (1 MHz) 0x90 / 0x48: NXP SECURE ELEMENT SE050 (1.7 MHz) 0xC2 / 0x61: TUSB320 USB1 (Type-C plug) (400 kHz) 0x62 / 0x31: FUSB303 USB2 (Type-C receptacle) (400 kHz)
GPIO1_IO0 [ALT5]
GPIO1_IO1 [ALT5]
ANATOP_OTG2_ID [ALT2]
UART1_RTS_B [ALT8]
ENET1_TX_EN (ULZ: KPP_COL2) -> WDOG2_WDOG_RST_B_DEB [ALT8]
CSI_DATA00 (ULZ: SD2_DATA0) -> GPIO4_IO21 [ALT5]
CSI_DATA01 (ULZ: SD2_DATA1) -> GPIO4_IO22 [ALT5]
ULZ: VDD_HIGH_IN
